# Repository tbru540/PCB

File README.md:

# PCB
AA Charger Custom PCB

I completely redesigned the board, incorporating a dedicated charging port chip to automatically manipulate D+ and D- for each type of device, as well as incorporated a more modern buck converter into the board itself instead of using an external buck converter module. I've also incorporated a switch to enable power to the USB with a built in LED indiciator, a fuse for overcurrent protection, a TVS diode to protect against voltage spikes, as well as a ferrite bead to suppress EMI. This board was created using KiCad 9.0. 

The files above contain the file to the schematic and the PCB. Also, I've included pictures of the schematic, PCB, and 3D model for easier viewing. The 3D model is a PNG file, while the pictures of the schematic and PCB are JPG files.

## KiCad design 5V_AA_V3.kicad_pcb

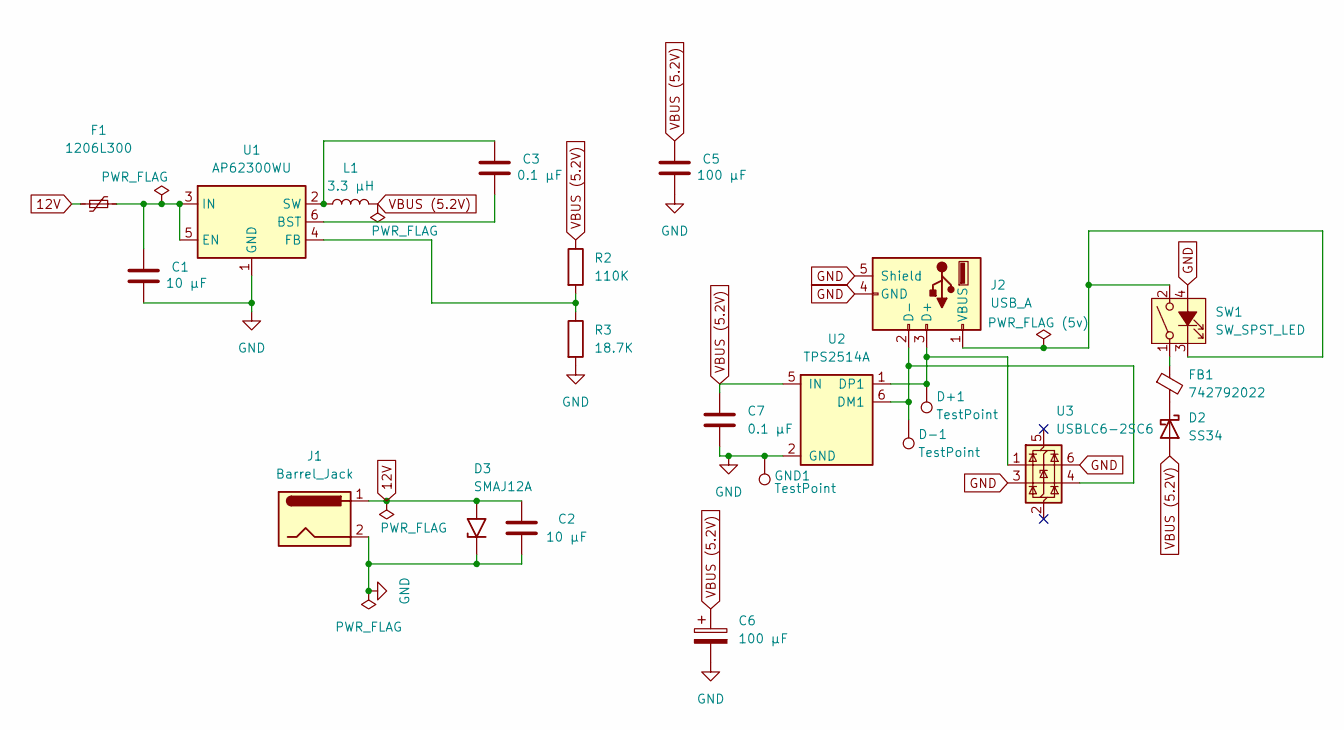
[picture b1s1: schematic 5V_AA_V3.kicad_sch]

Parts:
C1, C2: 10 µF; C_0805_2012Metric_Pad1.18x1.45mm_HandSolder
C3, C7: 0.1 µF; C_0805_2012Metric_Pad1.18x1.45mm_HandSolder
C5, C6: 100 µF; C_0805_2012Metric_Pad1.18x1.45mm_HandSolder
D2: SS34; D_SMA
D3: SMAJ12A; D_SMA_Handsoldering
D+1: TestPoint; TestPoint_Pad_D1.5mm
D-1: TestPoint; TestPoint_Pad_D1.5mm
F1: 1206L300; Fuse_1206_3216Metric_Pad1.42x1.75mm_HandSolder
FB1: 742792022; L_Walsin_WLFM201209x
GND1: TestPoint; TestPoint_Pad_D1.5mm
J1: Barrel_Jack; BarrelJack_CUI_PJ-063AH_Horizontal
J2: USB_A; USB_A_Receptacle_GCT_USB1046
L1: 3.3 µH; L_Taiyo-Yuden_NR-50xx_HandSoldering
R2: 110K; R_0805_2012Metric_Pad1.20x1.40mm_HandSolder
R3: 18.7K; R_0805_2012Metric_Pad1.20x1.40mm_HandSolder
SW1: SW_SPST_LED; SOP5_K8BU41_CNK
U1: AP62300WU; TSOT-23-6
U2: TPS2514A; SOT-23-6
U3: USBLC6-2SC6; SOT-23-6

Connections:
12V: C2.1, D3.2 (A2), F1.1, J1.1
GND: C1.1, C2.2, C5.1, C6.2, C7.2, D3.1 (A1), GND1.1, J1.2, J2.4 (GND), J2.5 (Shield), R3.2, SW1.4 (A), U1.1 (GND), U2.2 (GND), U3.3 (I/O2), U3.6 (I/O1)
unnamed: D2.1 (K), FB1.2
unnamed: FB1.1, SW1.1
unnamed: D+1.1, J2.3 (D+), U2.1 (DP1), U3.1 (I/O1)
unnamed: D-1.1, J2.2 (D-), U2.6 (DM1), U3.4 (I/O2)
unnamed: J2.1 (VBUS), SW1.2, SW1.3 (K)
unnamed: C3.1, U1.6 (BST)
unnamed: C1.2, F1.2, U1.3 (IN), U1.5 (EN)
unnamed: R2.2, R3.1, U1.4 (FB)
unnamed: C3.2, L1.1, U1.2 (SW)
VBUS (5.2V): C5.2, C6.1, C7.1, D2.2 (A), L1.2, R2.1, U2.5 (IN)

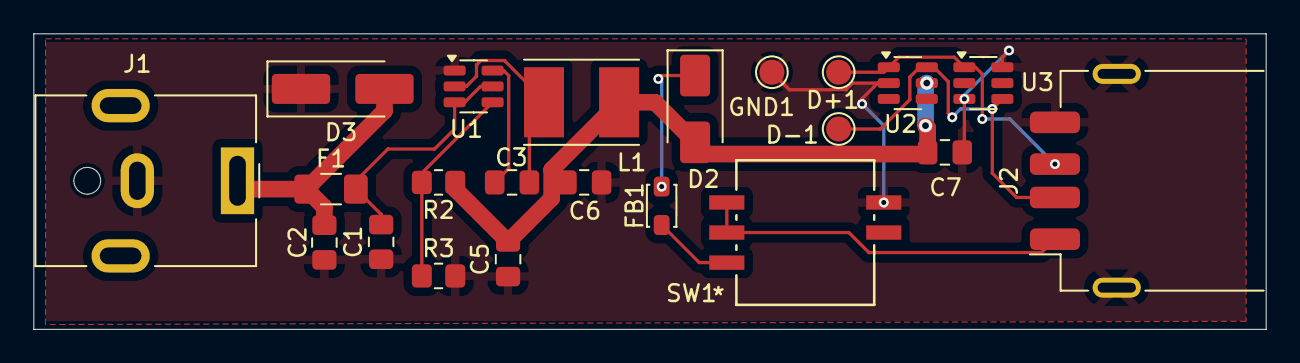
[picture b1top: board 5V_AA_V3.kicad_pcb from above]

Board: 2 copper layers, 73.8 x 17.7 mm, 22 parts (0 on the bottom side), 12 nets.

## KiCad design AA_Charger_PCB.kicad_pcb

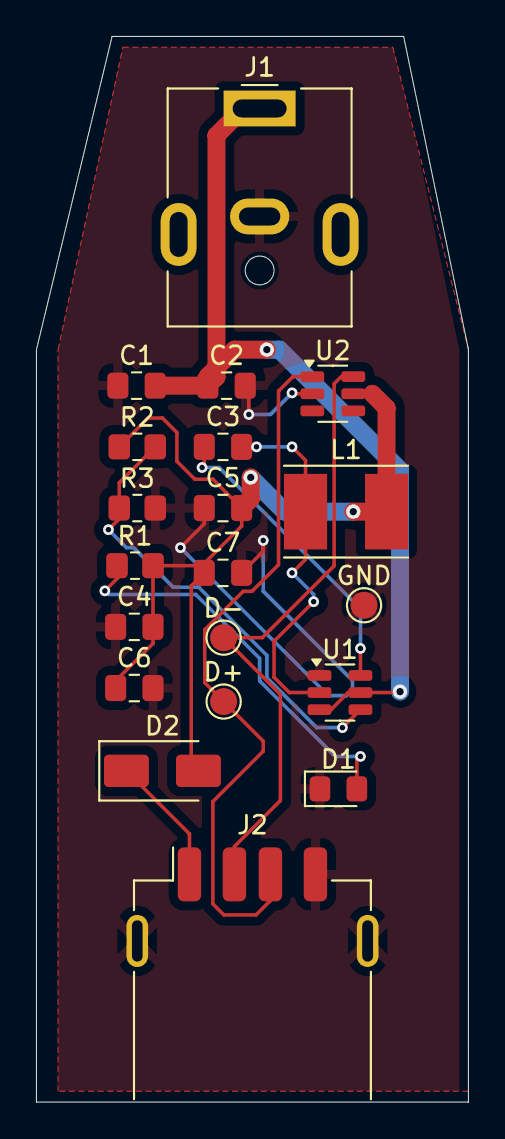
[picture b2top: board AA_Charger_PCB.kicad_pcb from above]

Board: 2 copper layers, 24.0 x 59.2 mm, 20 parts (0 on the bottom side), 10 nets.

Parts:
C1, C2, C4: 10 µF; C_0805_2012Metric_Pad1.18x1.45mm_HandSolder
C3, C7: 0.1 µF; C_0805_2012Metric_Pad1.18x1.45mm_HandSolder
C5, C6: 100 µF; C_0805_2012Metric_Pad1.18x1.45mm_HandSolder
D1: LED; LED_0805_2012Metric_Pad1.15x1.40mm_HandSolder
D2: SS34; D_SMA
D+: TestPoint; TestPoint_Pad_D1.5mm
D-: TestPoint; TestPoint_Pad_D1.5mm
GND: TestPoint; TestPoint_Pad_D1.5mm
J1: Barrel_Jack; BarrelJack_CUI_PJ-063AH_Horizontal
J2: USB_A; USB_A_Receptacle_GCT_USB1046
L1: 3.3 µH; L_Taiyo-Yuden_NR-50xx_HandSoldering
R1: 330; R_0805_2012Metric_Pad1.20x1.40mm_HandSolder
R2: 110K; R_0805_2012Metric_Pad1.20x1.40mm_HandSolder
R3: 18.7K; R_0805_2012Metric_Pad1.20x1.40mm_HandSolder
U1: AP62300WU; TSOT-23-6
U2: TPS2514A; SOT-23-6

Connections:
5.2V: C4.2, C5.2, C6.1, C7.1, D2.2 (A), L1.2, R1.2, R2.1, U2.5 (IN)
12V: C1.2, C2.1, J1.1, U1.3 (IN), U1.5 (EN)
GND: C1.1, C2.2, C4.1, C5.1, C6.2, C7.2, D1.1 (K), GND.1, J1.2, J2.4 (GND), J2.5 (Shield), R3.2, U1.1 (GND), U2.2 (GND)
unnamed: D1.2 (A), R1.1
unnamed: D2.1 (K), J2.1 (VBUS)
unnamed: D+.1, J2.3 (D+), U2.1 (DP1)
unnamed: D-.1, J2.2 (D-), U2.6 (DM1)
unnamed: C3.1, U1.6 (BST)
unnamed: R2.2, R3.1, U1.4 (FB)
unnamed: C3.2, L1.1, U1.2 (SW)

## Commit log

2025-07-31 Rename Schematic.png.jpg to Schematic.jpg
2025-07-31 Rename PCB.png.jpg to PCB.jpg
